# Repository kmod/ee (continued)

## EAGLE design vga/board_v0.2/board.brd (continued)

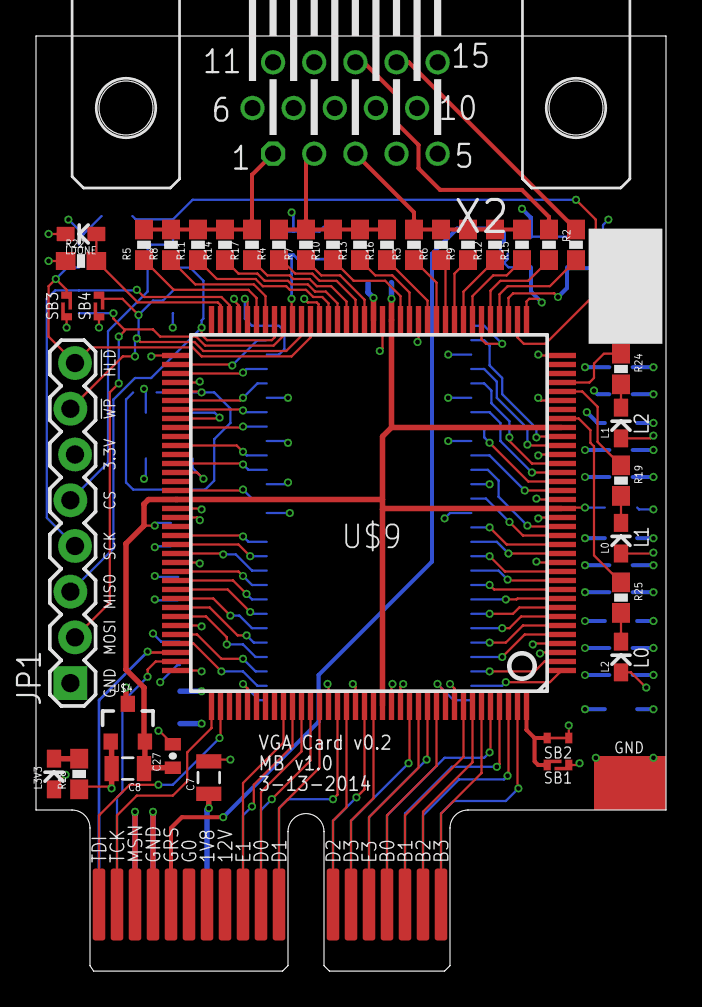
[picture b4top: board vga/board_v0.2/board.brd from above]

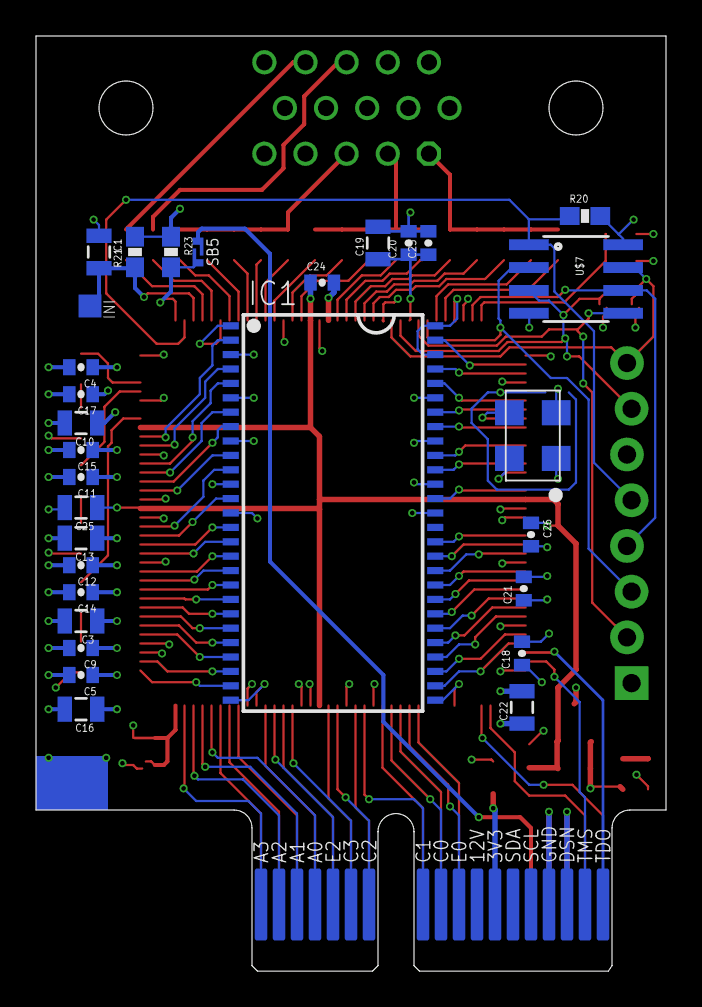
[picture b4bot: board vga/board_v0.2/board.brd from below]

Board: 4 copper layers, 35.0 x 52.0 mm, 70 parts (30 on the bottom side), 107 nets.

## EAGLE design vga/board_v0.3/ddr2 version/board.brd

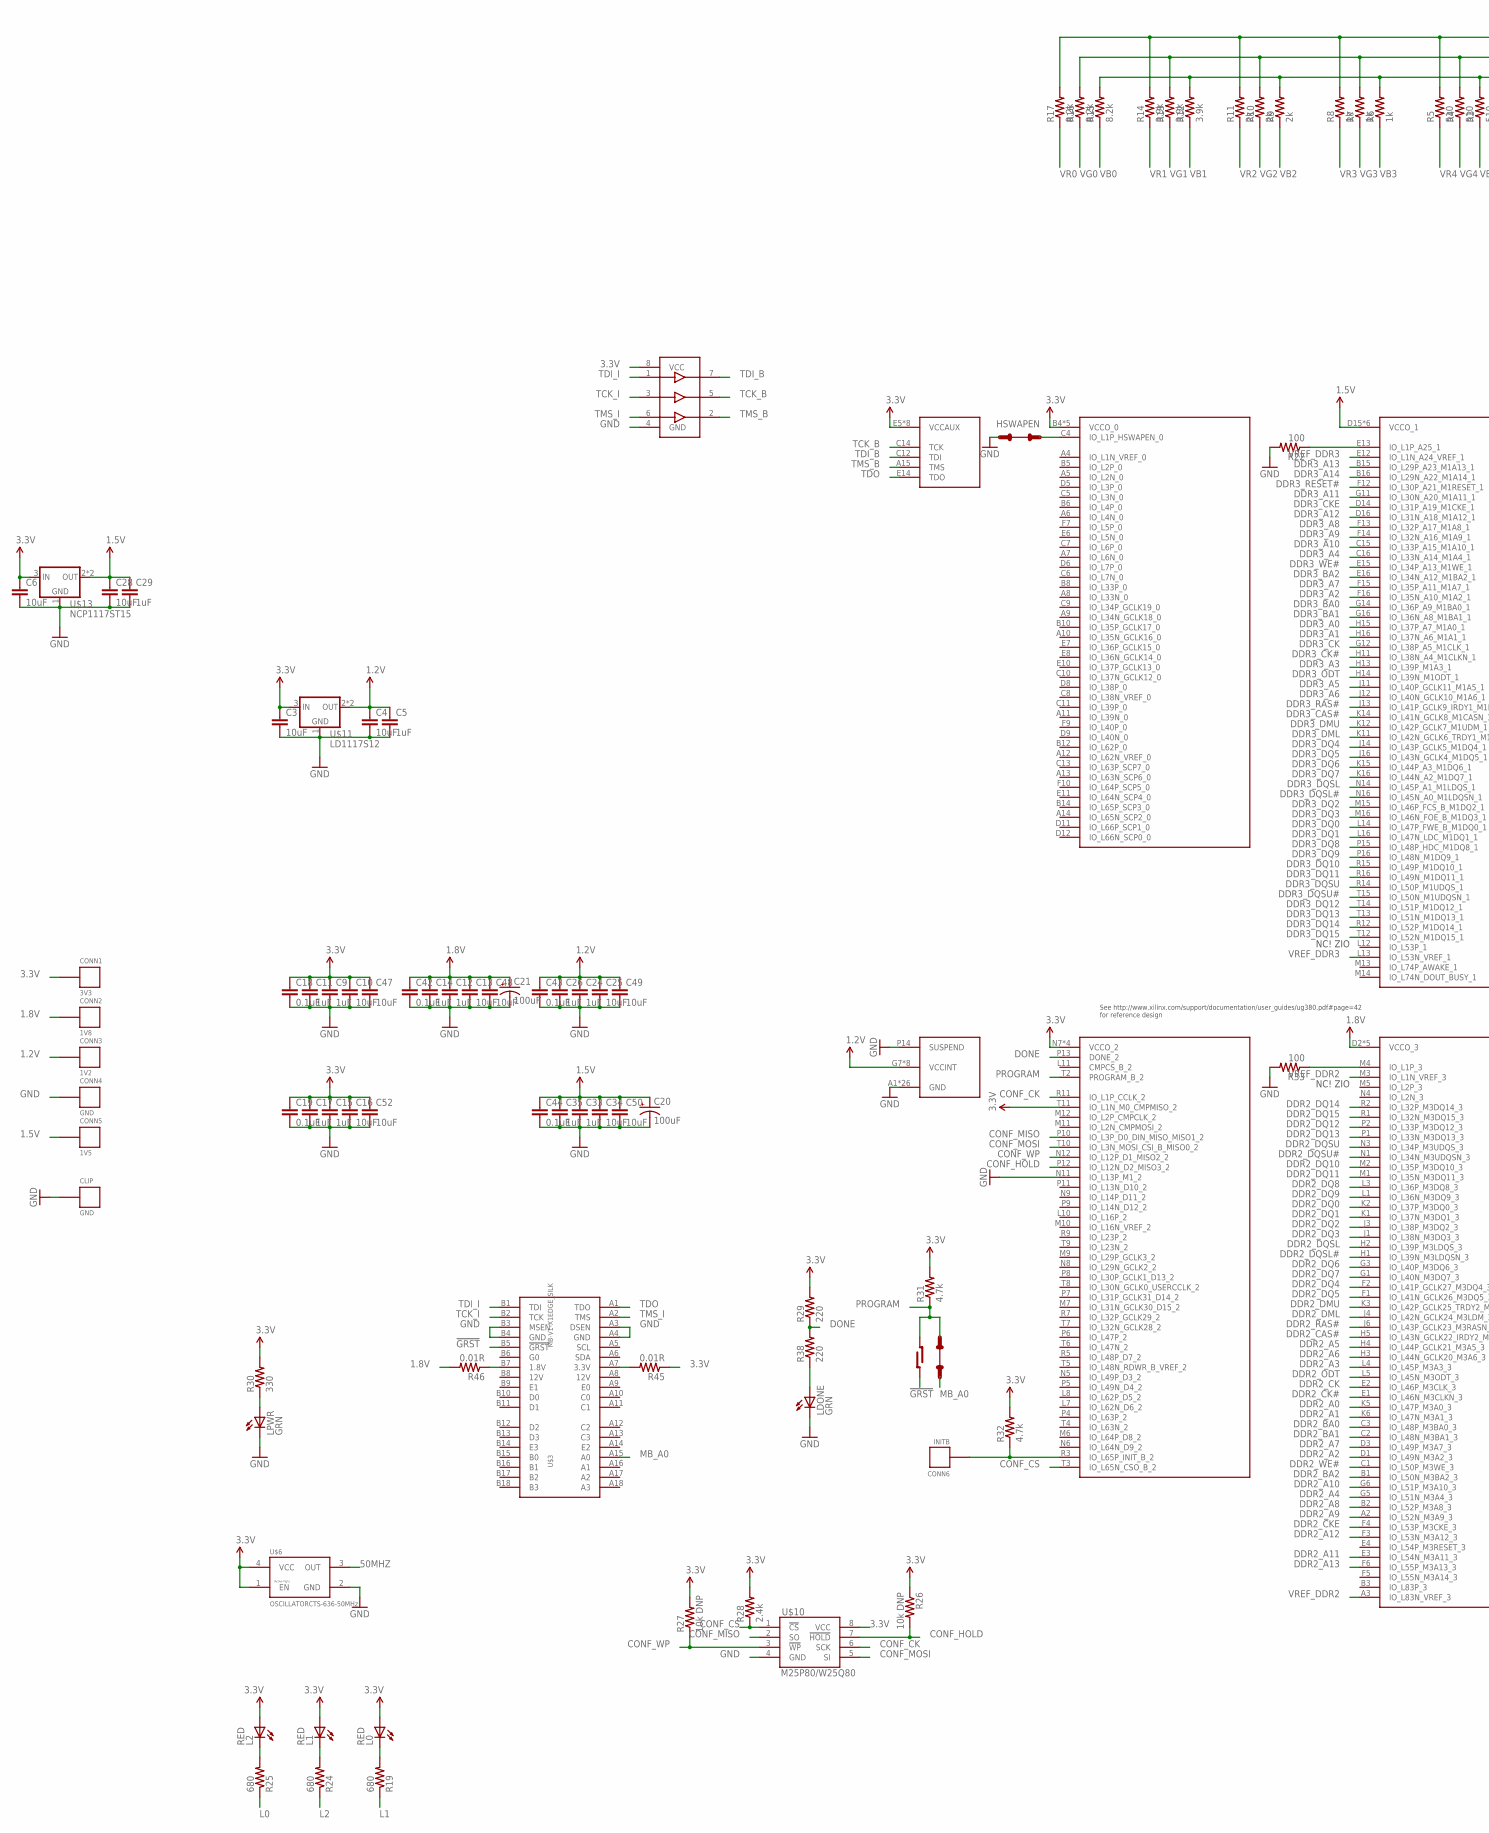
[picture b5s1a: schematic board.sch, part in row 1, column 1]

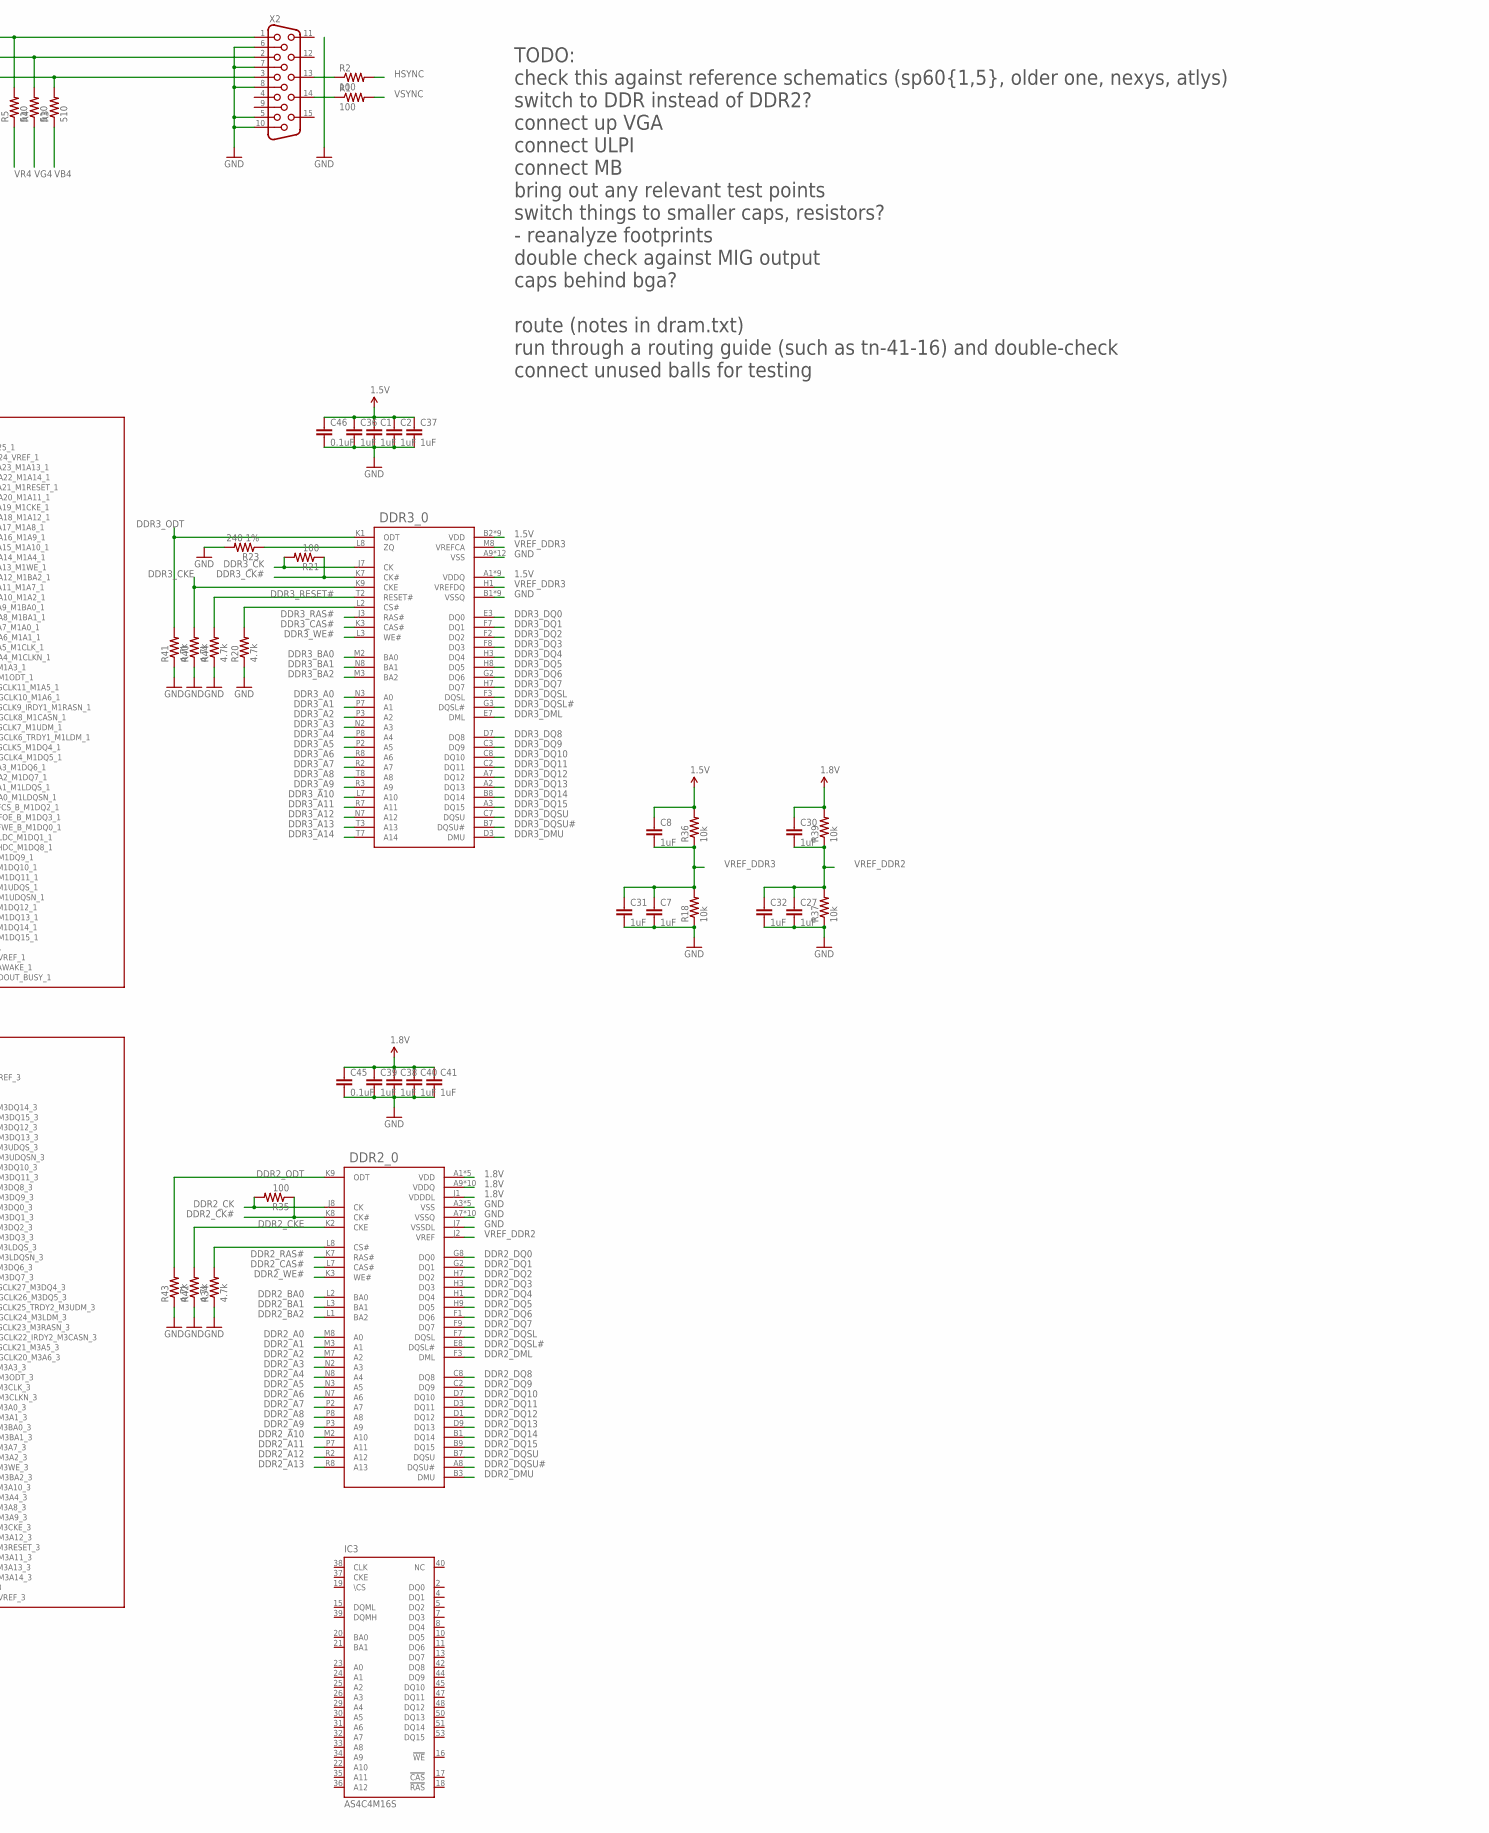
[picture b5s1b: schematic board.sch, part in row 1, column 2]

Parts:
C1, C2, C5, C7, C8, C9, C11, C12, C14, C15, C17, C24, C26, C27, C29, C30, C31, C32, C33, C35, C36, C37, C38, C39, C40, C41: 1uF; 0402-CAP
C3, C4, C6, C10, C13, C16, C25, C28, C34, C47, C48, C49, C50, C52: 10uF; 0603-CAP
C18, C19, C42, C43, C44, C45, C46: 0.1uF; C0201
C20, C21: 100uF; CAP-5-2
CLIP: GND; CLIP-AREA
CONN1: 3V3; HOLE_22AWG
CONN2: 1V8; HOLE_22AWG
CONN3: 1V2; HOLE_22AWG
CONN4: GND; HOLE_22AWG
CONN5: 1V5; HOLE_22AWG
CONN6: INITB; TESTPAD-1.27
DDR2_0: DDR2X16; BGA84
DDR3_0: DDR3X16; BGA96
IC1: XC6S{9,16,25}LX-FT256; XILINX_FT256
IC2: 74X3G34; TSSOP8
IC3: AS4C4M16S; TSOP54-400
L0, L1, L2: RED; 0603_LED
LDONE: GRN; 0603_LED
LPWR: GRN; 0603_LED
R1, R2, R21, R22, R33, R35: 100; 0603-RES
R3, R4, R5: 510; 0603-RES
R6, R7, R8: 1k; 0603-RES
R9, R10, R11: 2k; 0603-RES
R12, R13, R14: 3.9k; 0603-RES
R15, R16, R17: 8.2k; 0603-RES
R18, R36, R37, R39: 10k; 0603-RES
R19, R24, R25: 680; 0603-RES
R20, R34, R40, R41, R42, R43, R44: 4.7k; 0402-RES
R23: 240 1%; 0603-RES
R26, R27: 10k DNP; 0402-RES
R28: 2.4k; 0603-RES
R29, R38: 220; 0603-RES
R30: 330; 0603-RES
R31, R32: 4.7k; 0603-RES
R45, R46: 0.01R; 0603-RES
SB1: SOLDER-BRIDGEOPEN; SOLDER-BRIDGE-OPEN
SB2, SB5: TRACE-CUT
U$3: MB-V1-X1EDGE_SILK; MB-V1-X1-EDGE
U$6: OSCILLATORCTS-636-50MHz; CTS-636
U$10: M25P80/W25Q80; SO08
U$11: LD1117S12; SOT223
U$13: NCP1117ST15; SOT223
X2: HF15H; HDF15H

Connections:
1.2V: C4.1, C5.1, C24.1, C25.1, C26.1, C43.1, C49.1, CONN3.P, IC1.G7 (VCCINT), IC1.G9 (VCCINT), IC1.H8 (VCCINT), IC1.H10 (VCCINT), IC1.J7 (VCCINT), IC1.J9 (VCCINT), IC1.K8 (VCCINT), IC1.K10 (VCCINT), U$11.2 (OUT), U$11.4 (OUT)
1.5V: C1.1, C2.1, C8.1, C20.1 (+), C28.1, C29.1, C33.1, C34.1, C35.1, C36.1, C37.1, C44.1, C46.1, C50.1, CONN5.P, DDR3_0.A1 (VDDQ), DDR3_0.A8 (VDDQ), DDR3_0.B2 (VDD), DDR3_0.C1 (VDDQ), DDR3_0.C9 (VDDQ), DDR3_0.D2 (VDDQ), DDR3_0.D9 (VDD), DDR3_0.E9 (VDDQ), DDR3_0.F1 (VDDQ), DDR3_0.G7 (VDD), DDR3_0.H2 (VDDQ), DDR3_0.H9 (VDDQ), DDR3_0.K2 (VDD), DDR3_0.K8 (VDD), DDR3_0.N1 (VDD), DDR3_0.N9 (VDD), DDR3_0.R1 (VDD), DDR3_0.R9 (VDD), IC1.D15 (VCCO_1), IC1.G13 (VCCO_1), IC1.J15 (VCCO_1), IC1.K13 (VCCO_1), IC1.N15 (VCCO_1), IC1.R13 (VCCO_1), R36.2, U$13.2 (OUT), U$13.4 (OUT)
1.8V: C12.1, C13.1, C14.1, C21.1 (+), C30.1, C38.1, C39.1, C40.1, C41.1, C42.1, C45.1, C48.1, CONN2.P, DDR2_0.A1 (VDD), DDR2_0.A9 (VDDQ), DDR2_0.C1 (VDDQ), DDR2_0.C3 (VDDQ), DDR2_0.C7 (VDDQ), DDR2_0.C9 (VDDQ), DDR2_0.E1 (VDD), DDR2_0.E9 (VDDQ), DDR2_0.G1 (VDDQ), DDR2_0.G3 (VDDQ), DDR2_0.G7 (VDDQ), DDR2_0.G9 (VDDQ), DDR2_0.J1 (VDDDL), DDR2_0.J9 (VDD), DDR2_0.M9 (VDD), DDR2_0.R1 (VDD), IC1.D2 (VCCO_3), IC1.G4 (VCCO_3), IC1.J2 (VCCO_3), IC1.K4 (VCCO_3), IC1.N2 (VCCO_3), R39.2, R46.2
3.3V: C3.1, C6.1, C9.1, C10.1, C11.1, C15.1, C16.1, C17.1, C18.1, C19.1, C47.1, C52.1, CONN1.P, IC1.B4 (VCCO_0), IC1.B9 (VCCO_0), IC1.B13 (VCCO_0), IC1.D7 (VCCO_0), IC1.D10 (VCCO_0), IC1.E5 (VCCAUX), IC1.F8 (VCCAUX), IC1.F11 (VCCAUX), IC1.G10 (VCCAUX), IC1.H6 (VCCAUX), IC1.J10 (VCCAUX), IC1.L6 (VCCAUX), IC1.L9 (VCCAUX), IC1.N7 (VCCO_2), IC1.N10 (VCCO_2), IC1.R4 (VCCO_2), IC1.R8 (VCCO_2), IC1.T11 (IO_L1N_M0_CMPMISO_2), IC2.8 (VCC), L0.A, L1.A, L2.A, R26.1, R27.2, R28.2, R29.2, R30.2, R31.2, R32.2, R45.1, U$6.1 (EN), U$6.4 (VCC), U$10.8 (VCC), U$11.3 (IN), U$13.3 (IN)
50MHZ: U$6.3 (OUT)
!GRST: SB1.L1, SB1.L2, U$3.B5 (!GRST)
CONF_CK: IC1.R11 (IO_L1P_CCLK_2), U$10.6 (SCK)
CONF_CS: IC1.T3 (IO_L65N_CSO_B_2), R28.1, U$10.1 (!CS)
CONF_HOLD: IC1.P12 (IO_L12N_D2_MISO3_2), R26.2, U$10.7 (!HOLD)
CONF_MISO: IC1.P10 (IO_L3P_D0_DIN_MISO_MISO1_2), U$10.2 (SO)
CONF_MOSI: IC1.T10 (IO_L3N_MOSI_CSI_B_MISO0_2), U$10.5 (SI)
CONF_WP: IC1.N12 (IO_L12P_D1_MISO2_2), R27.1, U$10.3 (!WP)
DDR2_A0: DDR2_0.M8 (A0), IC1.K5 (IO_L47P_M3A0_3)
DDR2_A1: DDR2_0.M3 (A1), IC1.K6 (IO_L47N_M3A1_3)
DDR2_A2: DDR2_0.M7 (A2), IC1.D1 (IO_L49N_M3A2_3)
DDR2_A3: DDR2_0.N2 (A3), IC1.L4 (IO_L45P_M3A3_3)
DDR2_A4: DDR2_0.N8 (A4), IC1.G5 (IO_L51N_M3A4_3)
DDR2_A5: DDR2_0.N3 (A5), IC1.H4 (IO_L44P_GCLK21_M3A5_3)
DDR2_A6: DDR2_0.N7 (A6), IC1.H3 (IO_L44N_GCLK20_M3A6_3)
DDR2_A7: DDR2_0.P2 (A7), IC1.D3 (IO_L49P_M3A7_3)
DDR2_A8: DDR2_0.P8 (A8), IC1.B2 (IO_L52P_M3A8_3)
DDR2_A9: DDR2_0.P3 (A9), IC1.A2 (IO_L52N_M3A9_3)
DDR2_A10: DDR2_0.M2 (A10), IC1.G6 (IO_L51P_M3A10_3)
DDR2_A11: DDR2_0.P7 (A11), IC1.E3 (IO_L54N_M3A11_3)
DDR2_A12: DDR2_0.R2 (A12), IC1.F3 (IO_L53N_M3A12_3)
DDR2_A13: DDR2_0.R8 (A13), IC1.F6 (IO_L55P_M3A13_3)
DDR2_BA0: DDR2_0.L2 (BA0), IC1.C3 (IO_L48P_M3BA0_3)
DDR2_BA1: DDR2_0.L3 (BA1), IC1.C2 (IO_L48N_M3BA1_3)
DDR2_BA2: DDR2_0.L1 (BA2), IC1.B1 (IO_L50N_M3BA2_3)
DDR2_CAS#: DDR2_0.L7 (CAS#), IC1.H5 (IO_L43N_GCLK22_IRDY2_M3CASN_3)
DDR2_CK: DDR2_0.J8 (CK), IC1.E2 (IO_L46P_M3CLK_3), R35.2
DDR2_CK#: DDR2_0.K8 (CK#), IC1.E1 (IO_L46N_M3CLKN_3), R35.1
DDR2_CKE: DDR2_0.K2 (CKE), IC1.F4 (IO_L53P_M3CKE_3), R42.2
DDR2_DML: DDR2_0.F3 (DML), IC1.J4 (IO_L42N_GCLK24_M3LDM_3)
DDR2_DMU: DDR2_0.B3 (DMU), IC1.K3 (IO_L42P_GCLK25_TRDY2_M3UDM_3)
DDR2_DQ0: DDR2_0.G8 (DQ0), IC1.K2 (IO_L37P_M3DQ0_3)
DDR2_DQ1: DDR2_0.G2 (DQ1), IC1.K1 (IO_L37N_M3DQ1_3)
DDR2_DQ2: DDR2_0.H7 (DQ2), IC1.J3 (IO_L38P_M3DQ2_3)
DDR2_DQ3: DDR2_0.H3 (DQ3), IC1.J1 (IO_L38N_M3DQ3_3)
DDR2_DQ4: DDR2_0.H1 (DQ4), IC1.F2 (IO_L41P_GCLK27_M3DQ4_3)
DDR2_DQ5: DDR2_0.H9 (DQ5), IC1.F1 (IO_L41N_GCLK26_M3DQ5_3)
DDR2_DQ6: DDR2_0.F1 (DQ6), IC1.G3 (IO_L40P_M3DQ6_3)
DDR2_DQ7: DDR2_0.F9 (DQ7), IC1.G1 (IO_L40N_M3DQ7_3)
DDR2_DQ8: DDR2_0.C8 (DQ8), IC1.L3 (IO_L36P_M3DQ8_3)
DDR2_DQ9: DDR2_0.C2 (DQ9), IC1.L1 (IO_L36N_M3DQ9_3)
DDR2_DQ10: DDR2_0.D7 (DQ10), IC1.M2 (IO_L35P_M3DQ10_3)
DDR2_DQ11: DDR2_0.D3 (DQ11), IC1.M1 (IO_L35N_M3DQ11_3)
DDR2_DQ12: DDR2_0.D1 (DQ12), IC1.P2 (IO_L33P_M3DQ12_3)
DDR2_DQ13: DDR2_0.D9 (DQ13), IC1.P1 (IO_L33N_M3DQ13_3)
DDR2_DQ14: DDR2_0.B1 (DQ14), IC1.R2 (IO_L32P_M3DQ14_3)
DDR2_DQ15: DDR2_0.B9 (DQ15), IC1.R1 (IO_L32N_M3DQ15_3)
DDR2_DQSL: DDR2_0.F7 (DQSL), IC1.H2 (IO_L39P_M3LDQS_3)
DDR2_DQSL#: DDR2_0.E8 (DQSL#), IC1.H1 (IO_L39N_M3LDQSN_3)
DDR2_DQSU: DDR2_0.B7 (DQSU), IC1.N3 (IO_L34P_M3UDQS_3)
DDR2_DQSU#: DDR2_0.A8 (DQSU#), IC1.N1 (IO_L34N_M3UDQSN_3)
DDR2_ODT: DDR2_0.K9 (ODT), IC1.L5 (IO_L45N_M3ODT_3), R43.2
DDR2_RAS#: DDR2_0.K7 (RAS#), IC1.J6 (IO_L43P_GCLK23_M3RASN_3)
DDR2_WE#: DDR2_0.K3 (WE#), IC1.C1 (IO_L50P_M3WE_3)
DDR3_A0: DDR3_0.N3 (A0), IC1.H15 (IO_L37P_A7_M1A0_1)
DDR3_A1: DDR3_0.P7 (A1), IC1.H16 (IO_L37N_A6_M1A1_1)
DDR3_A2: DDR3_0.P3 (A2), IC1.F16 (IO_L35N_A10_M1A2_1)
DDR3_A3: DDR3_0.N2 (A3), IC1.H13 (IO_L39P_M1A3_1)
DDR3_A4: DDR3_0.P8 (A4), IC1.C16 (IO_L33N_A14_M1A4_1)
DDR3_A5: DDR3_0.P2 (A5), IC1.J11 (IO_L40P_GCLK11_M1A5_1)
DDR3_A6: DDR3_0.R8 (A6), IC1.J12 (IO_L40N_GCLK10_M1A6_1)
DDR3_A7: DDR3_0.R2 (A7), IC1.F15 (IO_L35P_A11_M1A7_1)
DDR3_A8: DDR3_0.T8 (A8), IC1.F13 (IO_L32P_A17_M1A8_1)
DDR3_A9: DDR3_0.R3 (A9), IC1.F14 (IO_L32N_A16_M1A9_1)
DDR3_A10: DDR3_0.L7 (A10), IC1.C15 (IO_L33P_A15_M1A10_1)
DDR3_A11: DDR3_0.R7 (A11), IC1.G11 (IO_L30N_A20_M1A11_1)
DDR3_A12: DDR3_0.N7 (A12), IC1.D16 (IO_L31N_A18_M1A12_1)
DDR3_A13: DDR3_0.T3 (A13), IC1.B15 (IO_L29P_A23_M1A13_1)
DDR3_A14: DDR3_0.T7 (A14), IC1.B16 (IO_L29N_A22_M1A14_1)
DDR3_BA0: DDR3_0.M2 (BA0), IC1.G14 (IO_L36P_A9_M1BA0_1)
DDR3_BA1: DDR3_0.N8 (BA1), IC1.G16 (IO_L36N_A8_M1BA1_1)
DDR3_BA2: DDR3_0.M3 (BA2), IC1.E16 (IO_L34N_A12_M1BA2_1)
DDR3_CAS#: DDR3_0.K3 (CAS#), IC1.K14 (IO_L41N_GCLK8_M1CASN_1)
DDR3_CK: DDR3_0.J7 (CK), IC1.G12 (IO_L38P_A5_M1CLK_1), R21.2
DDR3_CK#: DDR3_0.K7 (CK#), IC1.H11 (IO_L38N_A4_M1CLKN_1), R21.1
DDR3_CKE: DDR3_0.K9 (CKE), IC1.D14 (IO_L31P_A19_M1CKE_1), R40.2
DDR3_DML: DDR3_0.E7 (DML), IC1.K11 (IO_L42N_GCLK6_TRDY1_M1LDM_1)
DDR3_DMU: DDR3_0.D3 (DMU), IC1.K12 (IO_L42P_GCLK7_M1UDM_1)
DDR3_DQ0: DDR3_0.E3 (DQ0), IC1.L14 (IO_L47P_FWE_B_M1DQ0_1)
DDR3_DQ1: DDR3_0.F7 (DQ1), IC1.L16 (IO_L47N_LDC_M1DQ1_1)
DDR3_DQ2: DDR3_0.F2 (DQ2), IC1.M15 (IO_L46P_FCS_B_M1DQ2_1)
DDR3_DQ3: DDR3_0.F8 (DQ3), IC1.M16 (IO_L46N_FOE_B_M1DQ3_1)
DDR3_DQ4: DDR3_0.H3 (DQ4), IC1.J14 (IO_L43P_GCLK5_M1DQ4_1)
DDR3_DQ5: DDR3_0.H8 (DQ5), IC1.J16 (IO_L43N_GCLK4_M1DQ5_1)
DDR3_DQ6: DDR3_0.G2 (DQ6), IC1.K15 (IO_L44P_A3_M1DQ6_1)
DDR3_DQ7: DDR3_0.H7 (DQ7), IC1.K16 (IO_L44N_A2_M1DQ7_1)
DDR3_DQ8: DDR3_0.D7 (DQ8), IC1.P15 (IO_L48P_HDC_M1DQ8_1)
DDR3_DQ9: DDR3_0.C3 (DQ9), IC1.P16 (IO_L48N_M1DQ9_1)
DDR3_DQ10: DDR3_0.C8 (DQ10), IC1.R15 (IO_L49P_M1DQ10_1)
DDR3_DQ11: DDR3_0.C2 (DQ11), IC1.R16 (IO_L49N_M1DQ11_1)
DDR3_DQ12: DDR3_0.A7 (DQ12), IC1.T14 (IO_L51P_M1DQ12_1)
DDR3_DQ13: DDR3_0.A2 (DQ13), IC1.T13 (IO_L51N_M1DQ13_1)
DDR3_DQ14: DDR3_0.B8 (DQ14), IC1.R12 (IO_L52P_M1DQ14_1)
DDR3_DQ15: DDR3_0.A3 (DQ15), IC1.T12 (IO_L52N_M1DQ15_1)
DDR3_DQSL: DDR3_0.F3 (DQSL), IC1.N14 (IO_L45P_A1_M1LDQS_1)
DDR3_DQSL#: DDR3_0.G3 (DQSL#), IC1.N16 (IO_L45N_A0_M1LDQSN_1)
DDR3_DQSU: DDR3_0.C7 (DQSU), IC1.R14 (IO_L50P_M1UDQS_1)
DDR3_DQSU#: DDR3_0.B7 (DQSU#), IC1.T15 (IO_L50N_M1UDQSN_1)
DDR3_ODT: DDR3_0.K1 (ODT), IC1.H14 (IO_L39N_M1ODT_1), R41.2
DDR3_RAS#: DDR3_0.J3 (RAS#), IC1.J13 (IO_L41P_GCLK9_IRDY1_M1RASN_1)
DDR3_RESET#: DDR3_0.T2 (RESET#), IC1.F12 (IO_L30P_A21_M1RESET_1), R44.2
DDR3_WE#: DDR3_0.L3 (WE#), IC1.E15 (IO_L34P_A13_M1WE_1)
DONE: IC1.P13 (DONE_2), R29.1, R38.2
GND: C1.2, C2.2, C3.2, C4.2, C5.2, C6.2, C7.2, C9.2, C10.2, C11.2, C12.2, C13.2, C14.2, C15.2, C16.2, C17.2, C18.2, C19.2, C20.2 (-), C21.2 (-), C24.2, C25.2, C26.2, C27.2, C28.2, C29.2, C31.2, C32.2, C33.2, C34.2, C35.2, C36.2, C37.2, C38.2, C39.2, C40.2, C41.2, C42.2, C43.2, C44.2, C45.2, C46.2, C47.2, C48.2, C49.2, C50.2, C52.2, CLIP.P$1, CLIP.P$2, CONN4.P, DDR2_0.A3 (VSS), DDR2_0.A7 (VSSQ), DDR2_0.B2 (VSSQ), DDR2_0.B8 (VSSQ), DDR2_0.D2 (VSSQ), DDR2_0.D8 (VSSQ), DDR2_0.E3 (VSS), DDR2_0.E7 (VSSQ), DDR2_0.F2 (VSSQ), DDR2_0.F8 (VSSQ), DDR2_0.H2 (VSSQ), DDR2_0.H8 (VSSQ), DDR2_0.J3 (VSS), DDR2_0.J7 (VSSDL), DDR2_0.N1 (VSS), DDR2_0.P9 (VSS), DDR3_0.A9 (VSS), DDR3_0.B1 (VSSQ), DDR3_0.B3 (VSS), DDR3_0.B9 (VSSQ), DDR3_0.D1 (VSSQ), DDR3_0.D8 (VSSQ), DDR3_0.E1 (VSS), DDR3_0.E2 (VSSQ), DDR3_0.E8 (VSSQ), DDR3_0.F9 (VSSQ), DDR3_0.G1 (VSSQ), DDR3_0.G8 (VSS), DDR3_0.G9 (VSSQ), DDR3_0.J2 (VSS), DDR3_0.J8 (VSS), DDR3_0.M1 (VSS), DDR3_0.M9 (VSS), DDR3_0.P1 (VSS), DDR3_0.P9 (VSS), DDR3_0.T1 (VSS), DDR3_0.T9 (VSS), IC1.A1 (GND), IC1.A16 (GND), IC1.B7 (GND), IC1.B11 (GND), IC1.D4 (GND), IC1.D13 (GND), IC1.E9 (GND), IC1.G2 (GND), IC1.G8 (GND), IC1.G15 (GND), IC1.H7 (GND), IC1.H9 (GND), IC1.H12 (GND), IC1.J5 (GND), IC1.J8 (GND), IC1.K7 (GND), IC1.K9 (GND), IC1.L2 (GND), IC1.L15 (GND), IC1.M8 (GND), IC1.N11 (IO_L13P_M1_2), IC1.N13 (GND), IC1.P3 (GND), IC1.P14 (SUSPEND), IC1.R6 (GND), IC1.R10 (GND), IC1.T1 (GND), IC1.T16 (GND), IC2.4 (GND), LDONE.C, LPWR.C, R18.1, R20.1, R22.2, R23.2, R33.2, R34.1, R37.1, R40.1, R41.1, R42.1, R43.1, R44.1, SB5.R1, U$3.A3 (DSEN), U$3.A4 (GND), U$3.B3 (MSEN), U$3.B4 (GND), U$6.2 (GND), U$10.4 (GND), U$11.1 (GND), U$13.1 (GND), X2.5, X2.6, X2.7, X2.8, X2.10
HSWAPEN: IC1.C4 (IO_L1P_HSWAPEN_0), SB5.L1
HSYNC: R2.2
INIT_B: CONN6.P, IC1.R3 (IO_L65P_INIT_B_2), R32.1
L0: R25.1
L1: R19.1
L2: R24.1
MB_A0: SB2.L1, U$3.A15 (A0)
unnamed: R1.1, X2.14
unnamed: R2.1, X2.13
unnamed: R4.2, R7.2, R10.2, R13.2, R16.2, X2.2
unnamed: R5.2, R8.2, R11.2, R14.2, R17.2, X2.1
unnamed: R45.2, U$3.A7 (3.3V)
unnamed: L0.C, R19.2
unnamed: L1.C, R24.2
unnamed: L2.C, R25.2
unnamed: R3.2, R6.2, R9.2, R12.2, R15.2, X2.3
unnamed: IC1.E13 (IO_L1P_A25_1), R22.1
unnamed: DDR3_0.L8 (ZQ), R23.1
unnamed: DDR3_0.L2 (CS#), R20.2
unnamed: LPWR.A, R30.1
unnamed: R46.1, U$3.B7 (1.8V)
unnamed: LDONE.A, R38.1
unnamed: IC1.M4 (IO_L1P_3), R33.1
unnamed: DDR2_0.L8 (CS#), R34.2
PROGRAM: IC1.T2 (PROGRAM_B_2), R31.1, SB1.R1, SB1.R2, SB2.R1
TCK_B: IC1.C14 (TCK), IC2.5 (2Y)
TCK_I: IC2.3 (2A), U$3.B2 (TCK)
TDI_B: IC1.C12 (TDI), IC2.7 (1Y)
TDI_I: IC2.1 (1A), U$3.B1 (TDI)
TDO: IC1.E14 (TDO), U$3.A1 (TDO)
TMS_B: IC1.A15 (TMS), IC2.2 (3Y)
TMS_I: IC2.6 (3A), U$3.A2 (TMS)
VB0: R15.1
VB1: R12.1
VB2: R9.1
VB3: R6.1
VB4: R3.1
VG0: R16.1
VG1: R13.1
VG2: R10.1
VG3: R7.1
VG4: R4.1
VR0: R17.1
VR1: R14.1
VR2: R11.1
VR3: R8.1
VR4: R5.1
VREF_DDR2: C27.1, C30.2, C32.1, DDR2_0.J2 (VREF), IC1.A3 (IO_L83N_VREF_3), IC1.M3 (IO_L1N_VREF_3), R37.2, R39.1
VREF_DDR3: C7.1, C8.2, C31.1, DDR3_0.H1 (VREFDQ), DDR3_0.M8 (VREFCA), IC1.E12 (IO_L1N_A24_VREF_1), IC1.L13 (IO_L53N_VREF_1), R18.2, R36.1
VSYNC: R1.2

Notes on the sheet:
TODO: check this against reference schematics (sp60{1,5}, older one, nexys, atlys) switch to DDR instead of DDR2? connect up VGA connect ULPI connect MB bring out any relevant test points switch things to smaller caps, resistors? - reanalyze footprints double check against MIG output caps behind bg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
See http://www.xilinx.com/support/documentation/user_guides/ug380.pdf#page=42 for reference design
NC! ZIO

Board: 4 copper layers, 121 parts (7 on the bottom side), 137 nets, no tracks yet.
